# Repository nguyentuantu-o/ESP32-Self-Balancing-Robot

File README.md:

# ESP32-Self-Balancing-Robot
A two-wheeled self-balancing robot built with ESP32, MPU6050 IMU, DC motors, and encoder feedback. Focused on sensor fusion, state estimation, and feedback control.
## Hardware Design

### PCB 3D Preview

### Circuit Schematic

[View Schematic (PDF)](hardware/export/self-balancing.pdf)

### PCB Layout

[Top Layer](hardware/export/self-balancing-Front.svg) |
[Bottom Layer](hardware/export/self-balancing-Back.svg)  

### KiCad Source Files

[View KiCad Project](hardware/kicad/)

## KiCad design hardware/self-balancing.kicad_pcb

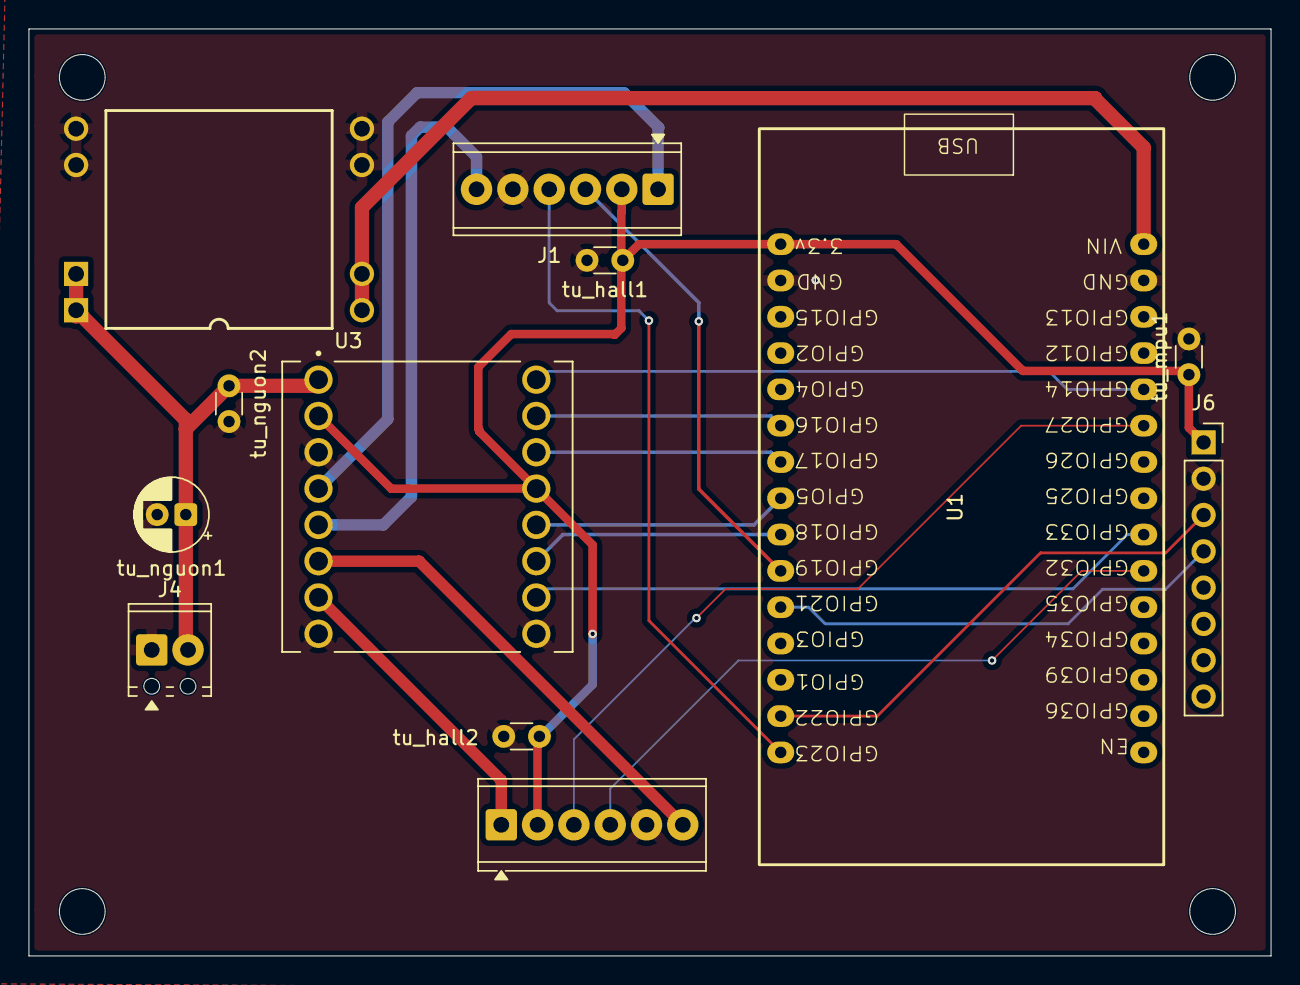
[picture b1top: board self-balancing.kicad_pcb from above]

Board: 4 copper layers, 86.9 x 64.9 mm, 12 parts (0 on the bottom side), 20 nets.

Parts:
J1: N20 Encoder L; TerminalBlock_Phoenix_MPT-0,5-6-2.54_1x06_P2.54mm_Horizontal
J2: MP1584EN
J4: Battery_2S_7.4V; TerminalBlock_Phoenix_MPT-0,5-2-2.54_1x02_P2.54mm_Horizontal
J5: N20 Encoder R; TerminalBlock_Phoenix_MPT-0,5-6-2.54_1x06_P2.54mm_Horizontal
J6: mpu 6050; PinSocket_1x08_P2.54mm_Vertical
U1: ESP32; ESP32_30pin
U3: TB6612FNG; MODULE_ROB-14450
tu_hall1, tu_hall2: 100nF; C_Disc_D3.0mm_W1.6mm_P2.50mm
tu_mpu1: 100nF; C_Disc_D3.0mm_W1.6mm_P2.50mm
tu_nguon1: 100mF; CP_Radial_D5.0mm_P2.00mm
tu_nguon2: 100nF; C_Disc_D3.0mm_W1.6mm_P2.50mm

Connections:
+5V: J2.1 (+OUT), J2.2 (+OUT), U1.1 (VIN)
/3.3V: J1.2, J5.2, J6.1, U1.16 (3.3v), U3.2 (VCC), U3.13 (STBY), tu_hall1.1, tu_hall2.1, tu_mpu1.1
/AI1: U1.22 (GPIO17), U3.14 (AI1)
/AI2: U1.21 (GPIO16), U3.15 (AI2)
/AO1: J1.6, U3.5 (A02)
/AO2: J1.1, U3.4 (A01)
/BI1: U1.23 (GPIO5), U3.12 (BI1)
/BI2: U1.24 (GPIO18), U3.11 (BI2)
/BO1: J5.6, U3.6 (B01)
/BO2: J5.1, U3.7 (B02)
/H1: J1.3, U1.25 (GPIO19)
/H2: J1.4, U1.30 (GPIO23)
/H3: J5.4, U1.10 (GPIO32)
/H4: J5.3, U1.6 (GPIO27)
/PWMA: U1.5 (GPIO14), U3.16 (PWMA)
/PWMB: U1.9 (GPIO33), U3.10 (PWMB)
/SCL: J6.3, U1.29 (GPIO22)
/SDA: J6.4, U1.26 (GPIO21)
GND: J1.5, J2.3 (-OUT), J2.4 (-OUT), J2.7 (-IN), J2.8 (-IN), J4.1, J5.5, J6.2, U1.2 (GND), U1.17 (GND), U3.3 (GND), U3.8 (GND), U3.9 (GND), tu_hall1.2, tu_hall2.2, tu_mpu1.2, tu_nguon1.2, tu_nguon2.2
VBAT: J2.5 (+IN), J2.6 (+IN), J4.2, U3.1 (VM), tu_nguon1.1, tu_nguon2.1
